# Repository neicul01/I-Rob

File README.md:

# I-Rob
Remote Roboter on ESP32 with MQTT
I-Rob
================================
Content of this project is a semi-autonomous robot system for academic teaching. The robot is remotely controlled from the base via the MQTT communication interface. 

Contents
--------

* Installation_
* `Limitations`_
* `Basestation`_
    * `RobotEsp32`_

* `Roboter`_
    * `I-Rob`_
* `Hardeware`_

Installation
------------

1. Install Mosquitto on your PC
2. Customize permission for Mosquitto folders
3. edit the config-file with the following lines

::
	allow_anonymous true
	listeners 1883
Now the Broker is available on Port 1883 and anonymous clients are allowed
4. open the application service and deactivate mosquitto
5. open cmd as admin and navigate to mosquitto folder. The following command is entered there:

::
   mosquitto -v -c mosquitto.conf

The mosquitto-python-library can be installed from here `paho.mqtt.python <https://github.com/eclipse/paho.mqtt.python>'_
More information can be found at `Mosquitto Website <https://mosquitto.org/documentation/authentication-methods/>`_ .
A helpfull tutorial can be found `here <http://www.steves-internet-guide.com/mossquitto-conf-file/>`_ .

Limitations
-----------------

The following feature are unimplemented.

Calibration of the line-sensors.

Basestation
-------------

Detailed API documentation is available through **pydoc**. Samples are available in the **examples** directory.

The package provides two modules, a full client and a helper for simple publishing.

RobotEsp32 userinstruction
**************************

The RobotEsp32 class contains all necessary functions for controlling and reading sensor data.

.. code:: python

    from paho.mqtt import client as mqtt_client
    import RobotEsp32 as classexample

    # The callback for when the client receives a CONNACK response from the server.
    examplebot = classexample.RobotEsp32( your broker IP-Adress, Port (optional if different from port 1883), subscriber-topic, publicher-topic)

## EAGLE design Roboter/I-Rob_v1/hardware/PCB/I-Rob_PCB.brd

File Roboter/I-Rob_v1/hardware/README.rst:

Please note that some parts of the Robot.step model come from external sources. These sources are referenced below:

    ESP32 modell https://print.grabcad.com/library/ai-thinker-nodemcu-32s-esp32-development-board-1
    
    Ultrasonic Sensor HC-SR04 https://grabcad.com/library/ultrasonic-sensor-hc-sr04-4/details?folder_id=10273199

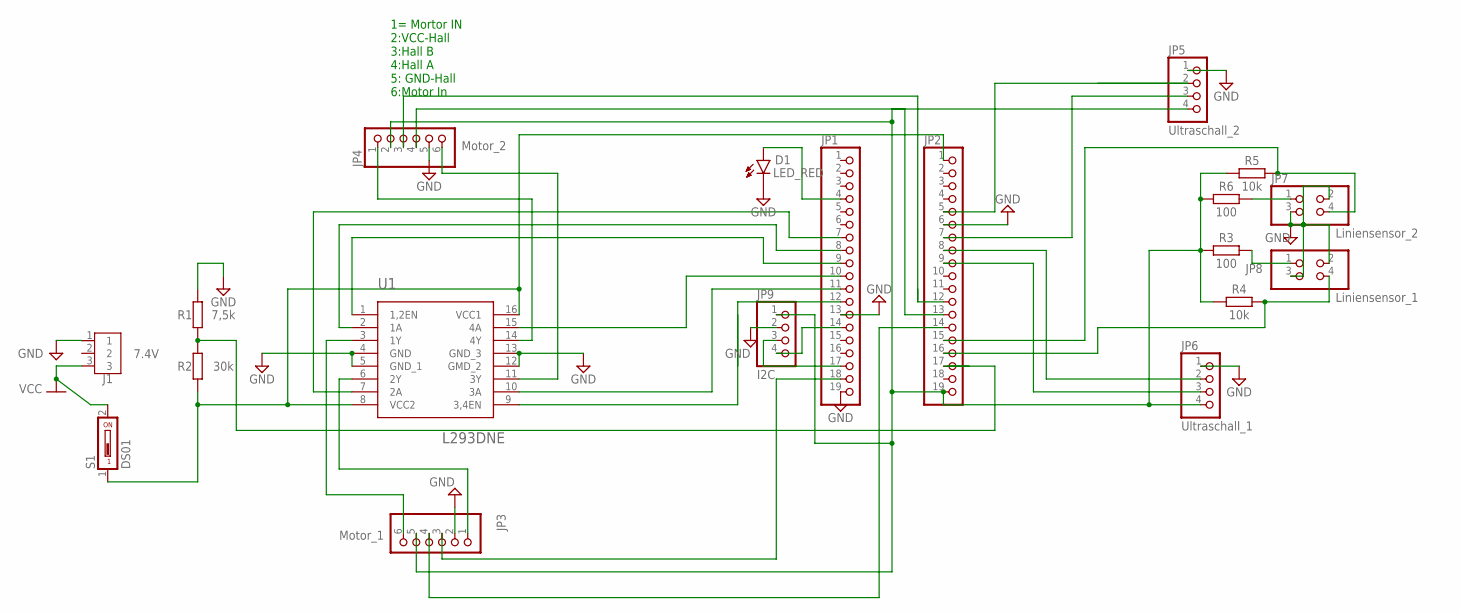
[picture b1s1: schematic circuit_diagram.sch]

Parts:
D1: LED_RED; LEDRD254W60D565H860B
J1: 7.4V; B3B-XH-A
JP1, JP2: PINHD-1X19; 1X19
JP3: Motor_1; 1X06
JP4: Motor_2; 1X06
JP5: Ultraschall_2; 1X04
JP6: Ultraschall_1; 1X04
JP7: Liniensensor_2; 2X02
JP8: Liniensensor_1; 2X02
JP9: I2C; 1X04
R1: 7,5k; RESAD724W46L381D178B
R2: 30k; RESAD724W46L381D178B
R3, R6: 100; RESAD724W46L381D178B
R4, R5: 10k; RESAD724W46L381D178B
S1: DS01; DS-01
U1: L293DNE; DIP-16_300MIL

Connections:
GND: D1.2 (C), J1.1, JP1.13, JP1.19, JP2.6, JP3.2, JP4.5, JP5.1, JP6.1, JP7.2, JP7.3, JP8.2, JP8.3, JP9.2, R1.2, U1.4 (GND), U1.5 (GND_1), U1.12 (GMD_2), U1.13 (GND_3)
unnamed: JP1.10, U1.15 (4A)
unnamed: JP1.11, U1.10 (3A)
unnamed: JP1.12, U1.9 (3,4EN)
unnamed: JP1.9, U1.1 (1,2EN)
unnamed: JP1.7, U1.7 (2A)
unnamed: JP1.8, U1.2 (1A)
unnamed: JP2.1, R2.1, S1.1, U1.8 (VCC2), U1.16 (VCC1)
unnamed: JP2.17, R1.1, R2.2
unnamed: JP4.6, U1.11 (3Y)
unnamed: JP4.1, U1.14 (4Y)
unnamed: JP3.6, U1.3 (1Y)
unnamed: JP3.1, U1.6 (2Y)
unnamed: JP2.19, JP3.5, JP4.2, JP5.4, JP6.4, JP9.1, R3.1, R4.1, R5.1, R6.1
unnamed: JP8.1, R3.2
unnamed: JP2.5, JP5.2
unnamed: JP7.1, R6.2
unnamed: JP2.15, JP7.4, R5.2
unnamed: JP2.16, JP8.4, R4.2
unnamed: D1.1 (A), JP1.4
unnamed: JP2.7, JP5.3
unnamed: JP2.8, JP6.2
unnamed: JP2.12, JP4.3
unnamed: JP2.9, JP6.3
unnamed: JP2.13, JP4.4
unnamed: JP2.14, JP3.4
unnamed: JP1.18, JP3.3
unnamed: JP1.17, JP9.3
unnamed: JP1.14, JP9.4
VCC: J1.3, S1.2

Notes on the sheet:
1= Mortor IN 2:VCC-Hall 3:Hall B 4:Hall A 5: GND-Hall 6:Motor In

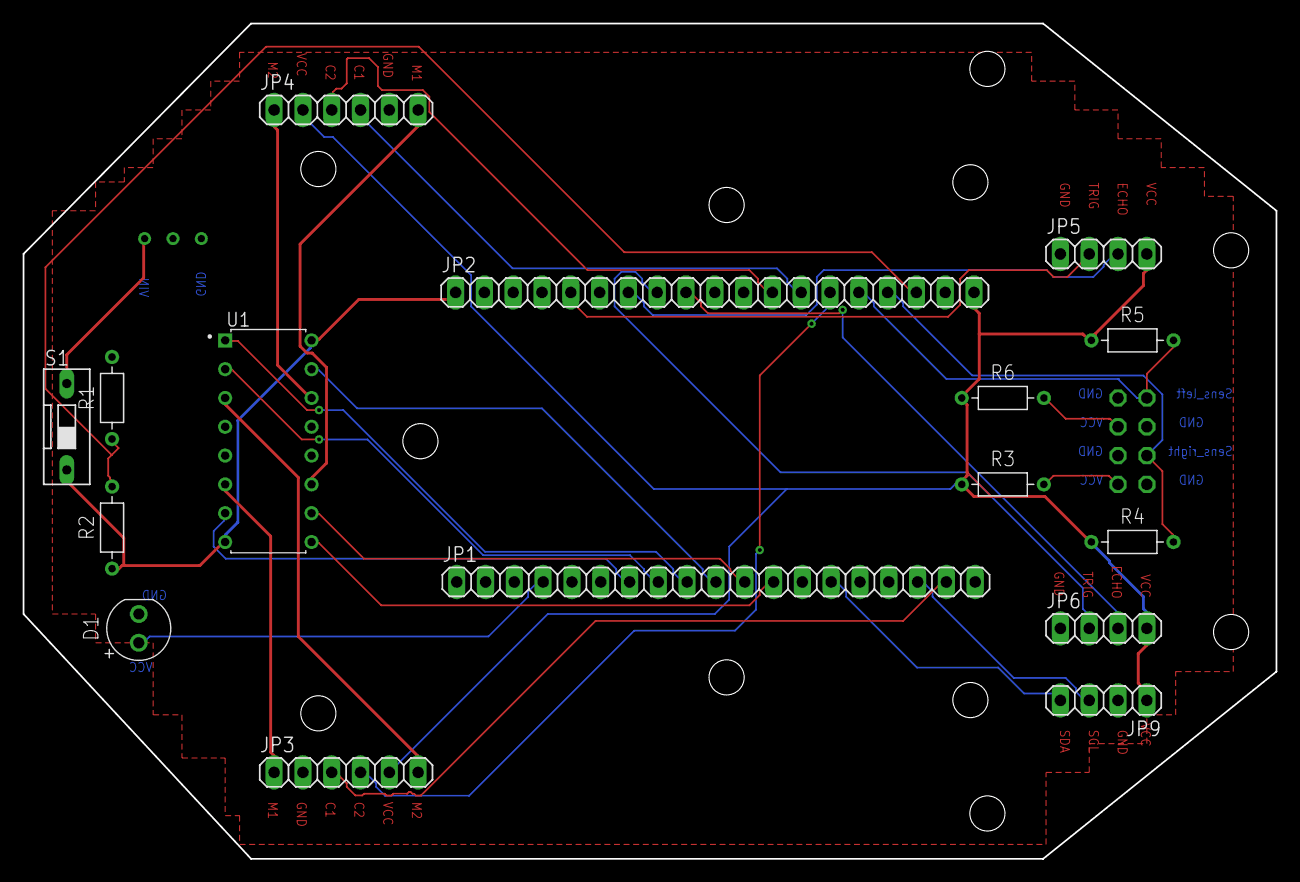
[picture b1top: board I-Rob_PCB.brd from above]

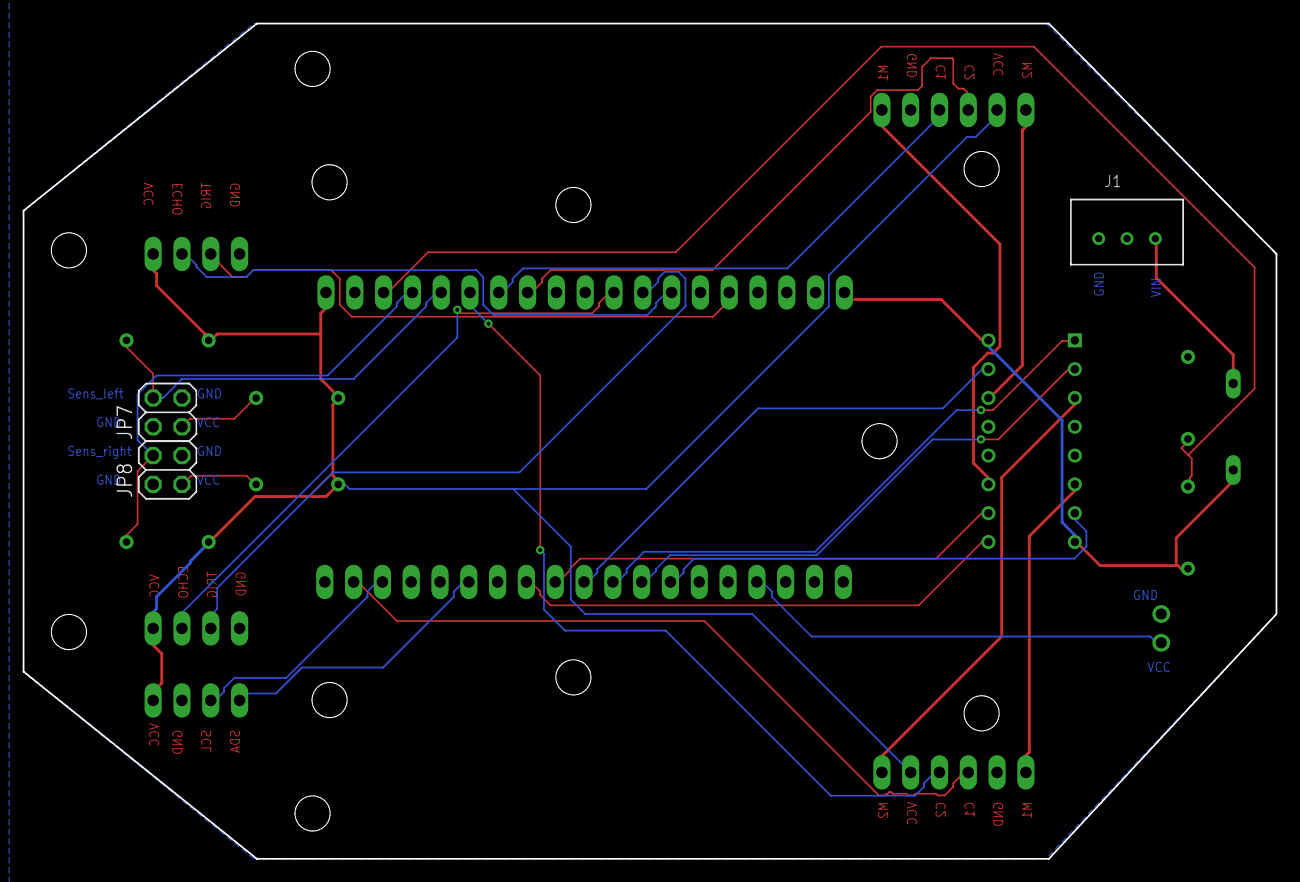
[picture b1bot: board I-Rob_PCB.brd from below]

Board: 2 copper layers, 110.5 x 73.7 mm, 19 parts (3 on the bottom side), 30 nets.

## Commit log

2021-12-03 Create t1
2021-12-03 Create t2
2021-12-03 Create r
2021-12-06 Create t
2021-12-07 Update LICENSE
2021-12-21 corrected typos.
